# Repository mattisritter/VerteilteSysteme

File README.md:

# Verteilte Systeme
## Heizkörperthermostat

### Software Overview
| Modul       | Zuständig   | Kommentare  | Probleme    |
|-------------|-------------|-------------|-------------|
| Timer0      | Mattis      ||||
| TMP75B      | Moritz      ||||
| WS2812      | Moritz      ||||
| Servo       | Mattis      ||||
| CAN         |||||
| Timer1      |             | output 100ms |              |

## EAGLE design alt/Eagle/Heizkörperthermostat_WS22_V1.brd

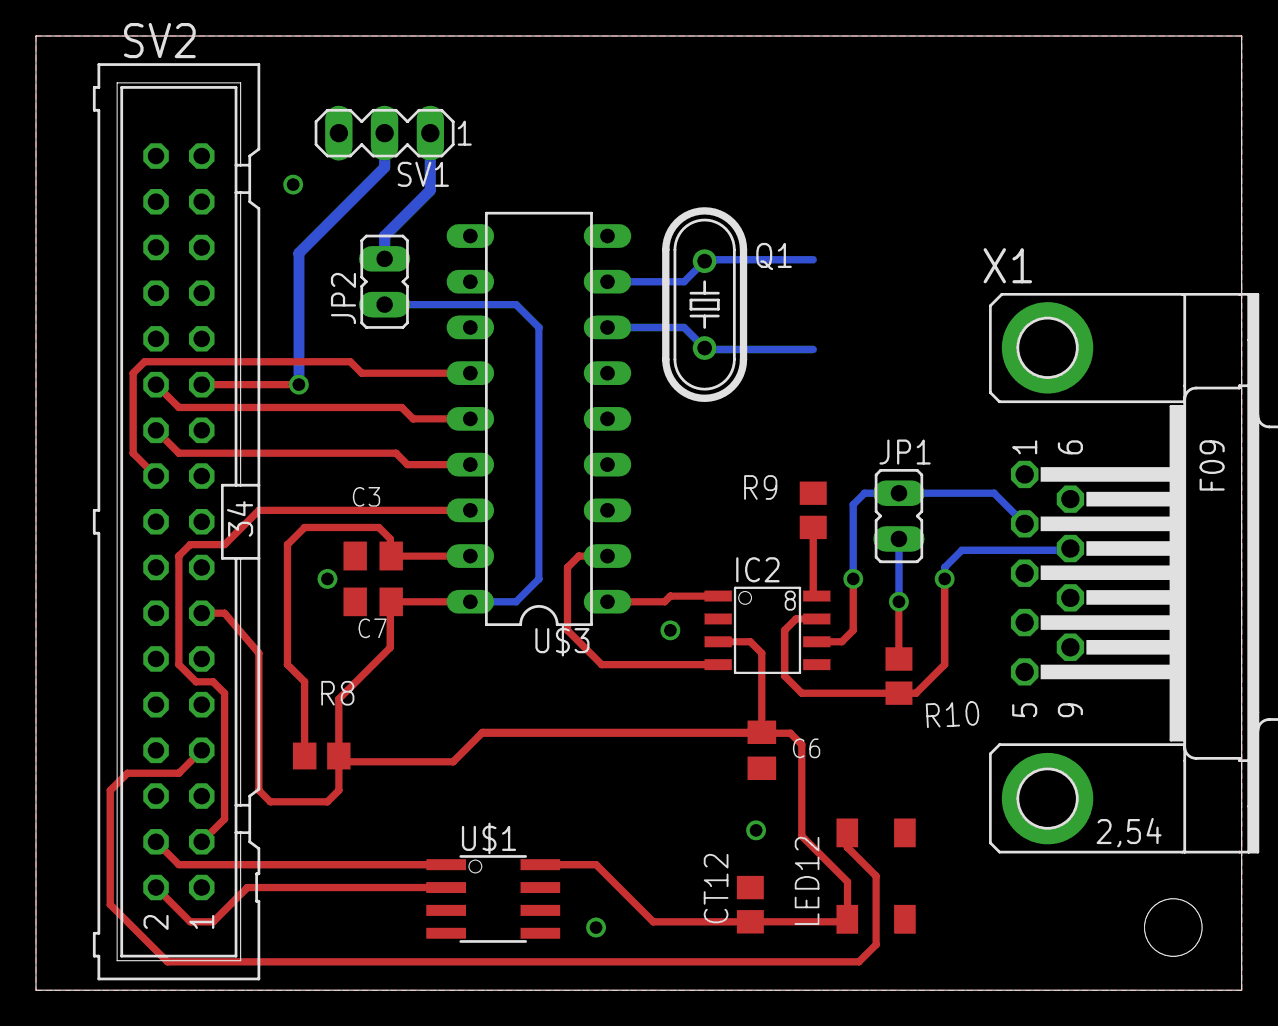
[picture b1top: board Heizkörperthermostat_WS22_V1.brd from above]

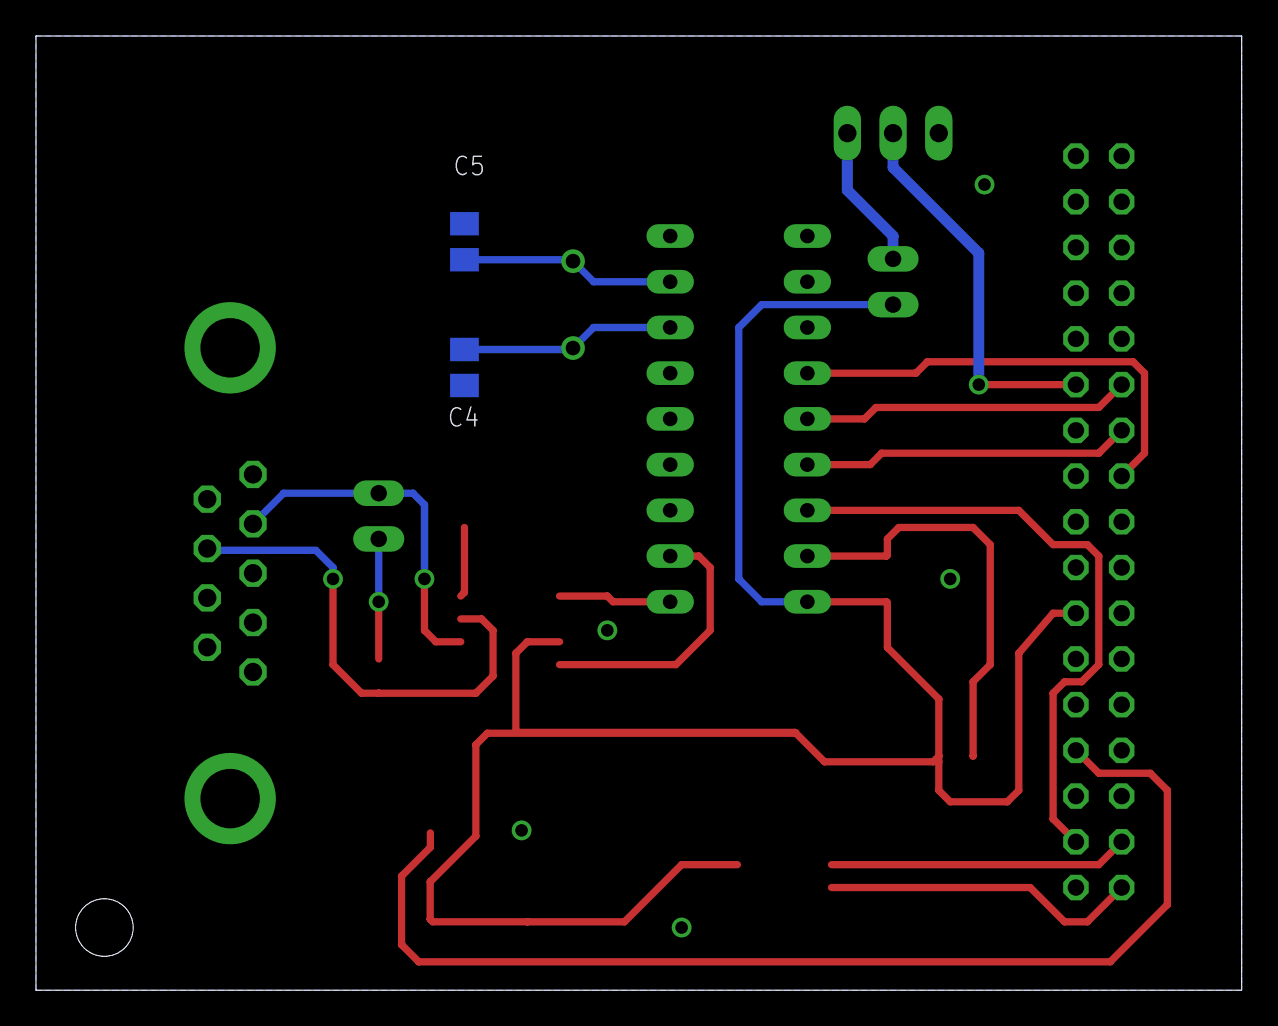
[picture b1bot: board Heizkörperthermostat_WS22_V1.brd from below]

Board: 2 copper layers, 67.0 x 53.0 mm, 19 parts (2 on the bottom side), 20 nets.

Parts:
C3, C6, C7: 100nF; C0805K
C4, C5: 22pF; C0805K
CT12: 100n; C0805
IC2: PCA82C251; SO8
JP1, JP2: JP1
LED12: WS2812_4H; WS2812_4
Q1: 16MHz; HC49/S
R8, R9: 10k; R0805
R10: 120; R0805
SV1: MA03-1
SV2: ML34
U$1: SO08
U$3: MCP2515PDIP; DIL18
X1: F09HP

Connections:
+5V: C6.1, C7.1, CT12.1, IC2.3, JP2.1, LED12.3, R8.2, SV2.13, U$1.8, U$3.18
GND: C3.2, C4.2, C5.2, C6.2, C7.2, CT12.2, IC2.2, LED12.1, R9.1, SV1.3, SV2.15, SV2.34, U$1.4, U$1.5, U$1.6, U$1.7, U$3.9, X1.3, X1.6
unnamed: C5.1, Q1.2, U$3.8
unnamed: C4.1, Q1.1, U$3.7
unnamed: C3.1, R8.1, U$3.17
unnamed: IC2.8, R9.2
unnamed: IC2.4, U$3.2
unnamed: IC2.1, U$3.1
unnamed: IC2.7, R10.2, X1.7
unnamed: JP1.1, R10.1
unnamed: IC2.6, JP1.2, X1.2
unnamed: JP2.2, SV1.1
PB3: SV2.24, U$3.14
PB4: SV2.22, U$3.15
PB5: SV2.20, U$3.13
PC4: SV2.4, U$1.1
PC5: SV2.2, U$1.2
PD0: SV2.3, U$3.16
PD2: LED12.2, SV2.7
PD6: SV1.2, SV2.23

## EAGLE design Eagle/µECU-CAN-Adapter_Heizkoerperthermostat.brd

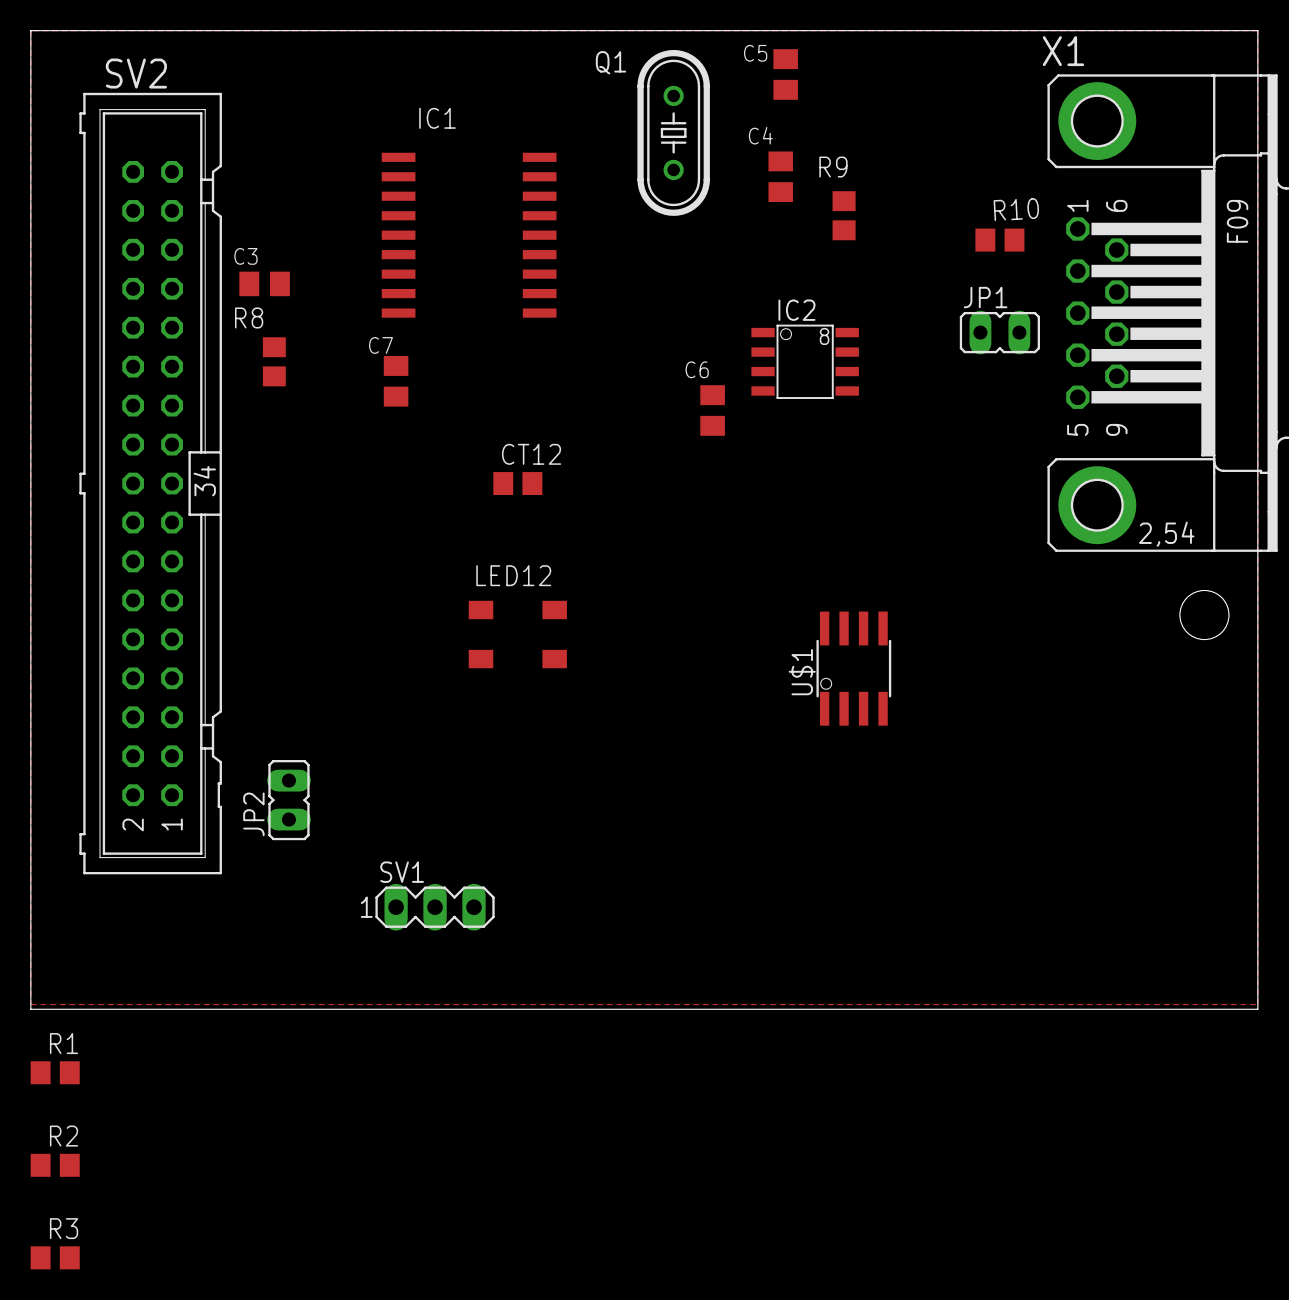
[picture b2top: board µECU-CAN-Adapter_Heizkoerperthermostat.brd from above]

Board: 2 copper layers, 80.0 x 63.8 mm, 22 parts (0 on the bottom side), 21 nets, no tracks yet.

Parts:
C3, C6, C7: 100nF; C0805K
C4, C5: 22pF; C0805K
CT12: 100n; C0805
IC1: MCP2515; SO-18DW
IC2: PCA82C251; SO8
JP1, JP2: JP1
LED12: WS2812_4H; WS2812_4
Q1: 16MHz; HC49/S
R1, R2, R3, R8, R9: 10k; R0805
R10: 120; R0805
SV1: MA03-1
SV2: ML34
U$1: SO08
X1: F09HP

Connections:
+5V: C6.1, C7.1, CT12.1, IC1.18, IC2.3, JP2.1, LED12.3, R1.2, R2.2, R3.2, R8.2, SV2.13, U$1.8
GND: C3.2, C4.2, C5.2, C6.2, C7.2, CT12.2, IC1.9, IC2.2, LED12.1, R9.1, SV1.3, SV2.15, SV2.34, U$1.4, U$1.5, U$1.6, U$1.7, X1.3, X1.6
unnamed: C5.1, IC1.8, Q1.2
unnamed: C4.1, IC1.7, Q1.1
unnamed: C3.1, IC1.17, R8.1
unnamed: IC2.8, R9.2
unnamed: IC1.2, IC2.4
unnamed: IC1.1, IC2.1
unnamed: IC2.7, R10.2, X1.7
unnamed: JP1.1, R10.1
unnamed: IC2.6, JP1.2, X1.2
unnamed: JP2.2, SV1.1
PB1: LED12.2, SV2.28
PB2: IC1.16, SV2.26
PB3: IC1.14, SV2.24
PB4: IC1.15, SV2.22
PB5: IC1.13, SV2.20
PC4: R2.1, SV2.4, U$1.1
PC5: R1.1, SV2.2, U$1.2
PD2: R3.1, SV2.7, U$1.3
PD6: SV1.2, SV2.23

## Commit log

2022-10-01 datasheets
2022-10-01 push code
2022-10-04 update code
2022-10-06 commit all
2022-10-07 rework board
2022-10-10 new can-controller
2022-10-10 Du Hu
2022-10-17 Powerpoint nach erster präsi
2022-10-17 alternative board
2022-10-17 edit lastenheft
    zweipunkt -> zu 5 punktregler
2022-10-18 HW review
2022-10-18 board nach hw review
2022-10-18 update1 hw review
2022-10-18 Update2
2022-10-18 Update3
2022-10-18 changes in 5V route
2022-10-24 sw-overview
2022-10-24 alles mögliche
2022-10-25 add petres eagle file
2022-10-26 main.h added
2022-10-26 switch of code optimization
2022-10-26 adjustment main
2022-10-26 main.h included
2022-10-26 included main.h
2022-10-26 cleaned git addings form sourcecode
2022-10-26 tmp75 twi changes
2022-10-26 seperate twi
2022-10-26 init header changed
2022-10-26 many remaining issues
2022-10-27 einfügen h und c dateien
2022-10-27 added several h/c; added main code
2022-10-27 viele fehler
2022-10-28 excluded can
2022-11-01 major changes to main program
2022-11-02 led into main
2022-11-05 temp sensor inbetriebnahme
2022-11-05 regler implementiert
2022-11-07 add servo
2022-11-08 code
2022-11-14 increase accuracy for rounding and improve display output
2022-11-15 modbas
2022-11-22 präsi
2022-11-23 carplant carsimmode sprungantwort regelparameter
2022-11-28 dies das
2022-11-29 präsi modbas
2022-11-29 verteilte systeme und modbas
2022-12-02 modbas sollgeschwindigkeit
2022-12-03 matlab und code für ansgar
2022-12-03 fehler in ex6_1 behoben
2022-12-03 nur ein sternchen eingefügt
2022-12-03 8.1 und 8.3
2022-12-04 madbas
2022-12-07 modbas doku
2022-12-12 modbas 9
2022-12-13 pathcontroller
2022-12-19 rechtschreibung
2022-12-20 baba doxygen doku
2022-12-20 Doxygen
2023-01-02 doku
2023-01-04 VS doku
2023-01-05 Verteilte Systeme
2023-01-06 update doku
2023-01-11 doku vs
2023-01-12 taster implementierung
2023-01-13 update matlab
2023-01-13 Präsentation und kommentare im code
2023-01-13 bilder jannis + rechtschreibfehler code
2023-01-14 Doxygen kommentare + doxygen in doku
2023-01-14 flussdiagramm
2023-01-14 pdf verteilte systeme
2023-01-14 verteilte systeme präsi
2023-01-15 bilder matlab
2023-01-15 uvp1
2023-01-15 no message
2023-04-02 seminararbeit
2023-04-20 report
2023-04-20 created Seminararbeit
2023-04-20 requirements
2023-04-20 requirments
2023-04-20 requirements Korrektur
2023-04-25 neue ordnerstruktur
2023-04-25 ki + referenzen
2023-04-26 ki update
2023-04-26 update ki
2023-05-15 nn erweitert
2023-05-18 mes + fischertechnik
2023-05-18 nn + referenzen
2023-05-20 ordner
2023-05-20 KI-campus
2023-05-20 was fehlt
2023-05-20 ki c
2023-05-20 add bilder
2023-05-21 move notes
2023-06-03 literature
2023-06-03 dark image
2023-06-03 beschreibung app und ergebnisse
2023-06-03 add quelle
2023-06-05 induktion sensor
2023-06-05 ampel
2023-06-05 report esd
2023-06-05 SPELLING!!!!!!!
2023-06-07 esd report
2023-06-07 pics
2023-06-07 update robo
2023-06-15 discussion
2023-06-15 flowchart
2023-06-15 update thesis
2023-06-15 table
2023-06-18 push
2023-06-18 what can you learn, british english in exercise step by step
2023-06-18 penis
2023-06-19 create ai group project
2023-06-20 esd table
2023-06-20 srceenshots
2023-06-20 more screenshots
2023-06-20 Update Report esd
2023-06-20 rueckpush
2023-06-25 das ergebnis langer qualen
2023-06-26 scrrenshots
2023-06-27 report ai
2023-06-27 html
2023-06-27 reports ai, esd
2023-06-28 dies das ananas
2023-06-28 AI final
2023-06-28 trajectory planning
2023-06-28 robo
2023-06-28 simulation
2023-06-28 robo report
2023-06-28 update theory
2023-06-28 get a kick
2023-06-29 AI finished
2023-06-29 matlab files
2023-06-29 improve abstract
2023-06-29 appendix
2023-06-30 robotics präsi
2023-06-30 problem statement
2023-06-30 video bilder
2023-06-30 i want du commit sui....
2023-07-01 robo bericht
2023-07-01 test q4
2023-07-03 knowledge transfer
2023-07-04 alle projekte fertig aminakoyum
2023-07-05 nummerierung
2023-07-05 paper template
2023-07-05 seminar
2023-07-05 rpmme
2023-07-05 paper
2023-07-06 v3.1
2023-07-13 Juli 2021
2023-07-17 IP exam
